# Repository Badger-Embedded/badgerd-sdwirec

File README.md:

# Badgerd SDWireC
[SDWireC](https://badgerd.nl/sdwirec) is a yet another implementation of SDWire of Tizen. In our design we used USB-C interface to interact with the host device or in other words Test Server(TS).

In **sdwirec-hw** folder, you can find the KiCAD project files of SDWireC, hardware design mostly based on Tizen but we changed some of the components since they are out of stock today.

In **sdwirec-sw** folder, you will find the clone of https://git.tizen.org/cgit/tools/testlab/sd-mux which has the software that you need to interact with SDWireC.

## Please follow the instructions in [Quick Start Guide](https://badgerd.nl/sdwirec/#quick-start) to give SDWireC a kickstart!

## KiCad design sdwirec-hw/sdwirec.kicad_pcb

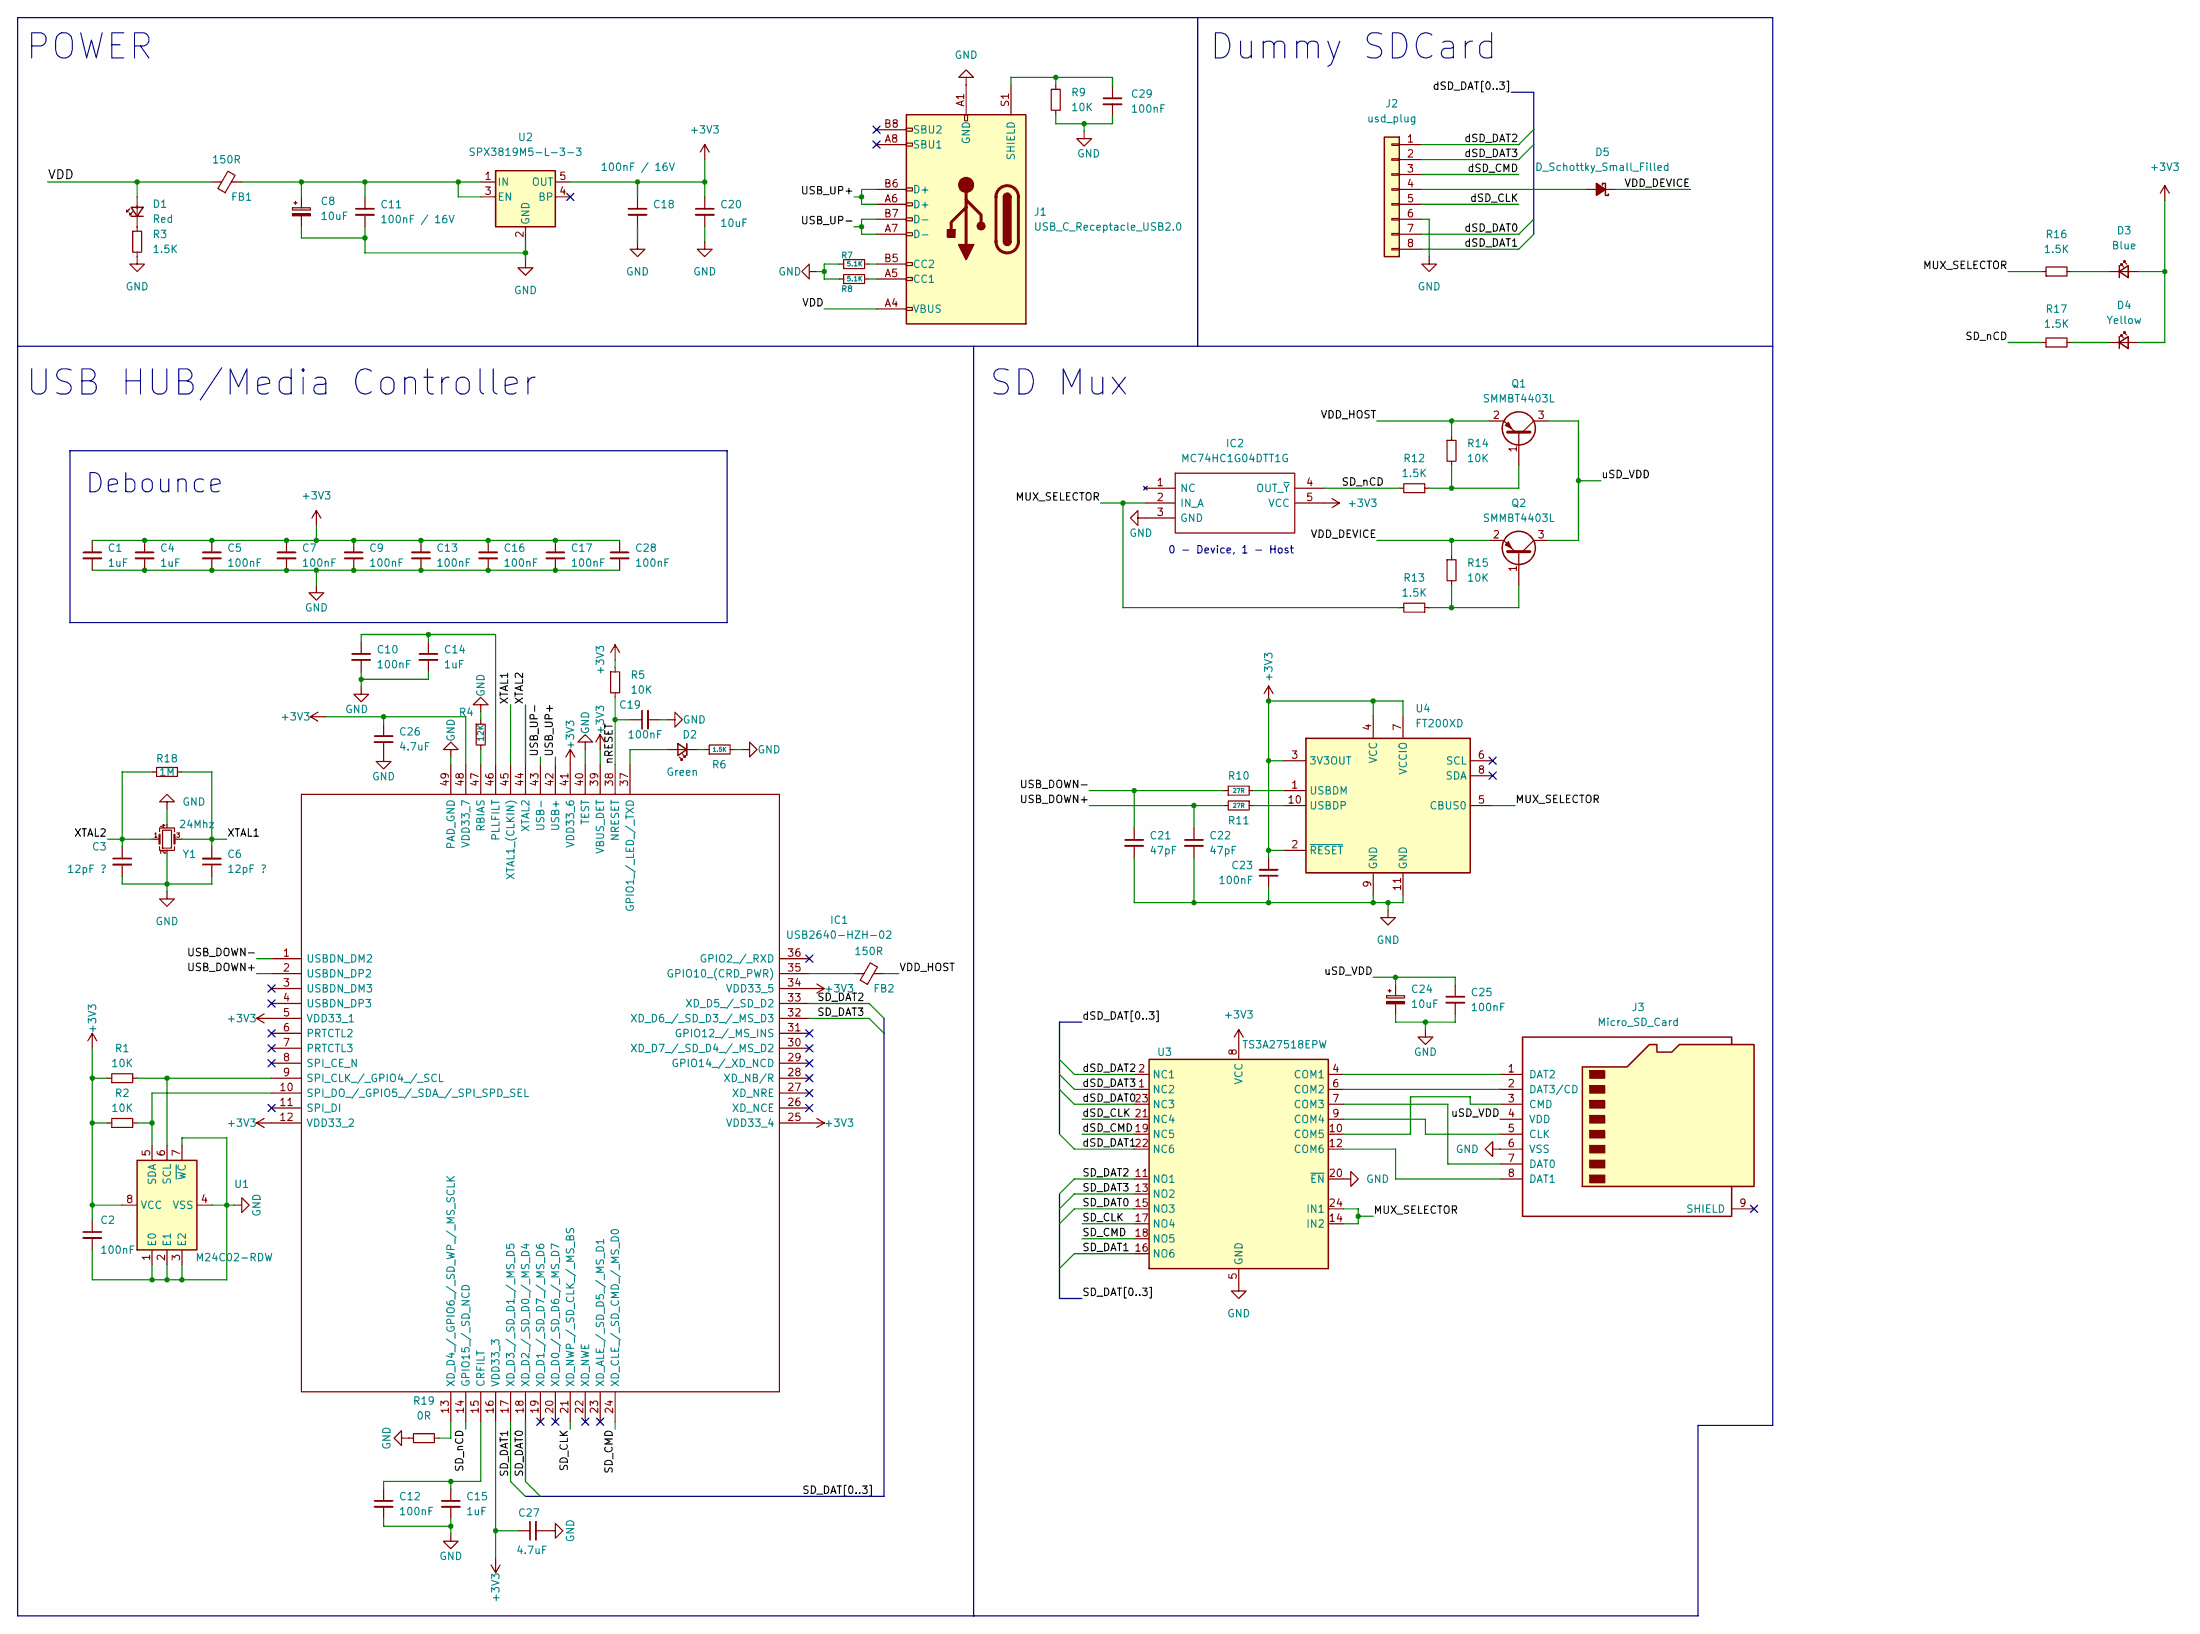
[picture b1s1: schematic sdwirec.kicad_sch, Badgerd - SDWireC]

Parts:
C1, C4, C14, C15: 1uF; C_0603_1608Metric; JLC 0603
C2, C5, C7, C9, C10, C12, C13, C16, C17, C19, C23, C25, C28: 100nF; C_0402_1005Metric; JLC 0402
C3, C6: 12pF ?; C_0402_1005Metric; JLC 0402
C8, C24: 10uF; CP_EIA-3216-18_Kemet-A; JLC CASE-A-3216
C11, C18: 100nF / 16V; C_0402_1005Metric; JLC 0402
C20: 10uF; C_0603_1608Metric; JLC 0603
C21, C22: 47pF; C_0402_1005Metric; JLC 0402
C26, C27: 4.7uF; C_0603_1608Metric; JLC 0603
C29: 100nF; C_0402_1005Metric
D1: Red; LED_0402_1005Metric; JLC 0402
D2: Green; LED_0402_1005Metric; JLC 0402
D3: Blue; LED_0402_1005Metric; JLC 0402
D4: Yellow; LED_0402_1005Metric; JLC 0402
D5: D_Schottky_Small_Filled; D_0402_1005Metric; LCSC Part C2837790
FB1, FB2: 150R; D_0603_1608Metric; JLC 0603
IC1: USB2640-HZH-02; QFN50P700X700X100-49N-D; Mouser Part Number 886-USB2640-HZH-02
IC2: MC74HC1G04DTT1G; SOT95P275X110-5N; Mouser Part Number 863-MC74HC1G04DTT1G
J1: USB_C_Receptacle_USB2.0; USB_C_Receptacle_GCT_USB4105-xx-A_16P_TopMnt_Horizontal; JLC SMD
J2: usd_plug; usd
J3: Micro_SD_Card; 5031821852; LCSC Part C587953
Q1, Q2: SMMBT4403L; SOT-23-3; JLC SOT-23-3
R1, R2, R5, R9, R14, R15: 10K; R_0402_1005Metric; JLC 0402
R3, R6, R12, R13, R16, R17: 1.5K; R_0402_1005Metric; JLC 0402
R4: 12K; R_0402_1005Metric; JLC 0402
R7, R8: 5.1K; R_0402_1005Metric; LCSC Part C25905
R10, R11: 27R; R_0402_1005Metric; JLC 0402
R18: 1M; R_0402_1005Metric
R19: 0R; R_0402_1005Metric; JLC 0402
U1: M24C02-RDW; TSSOP-8_4.4x3mm_P0.65mm; JLC TSSOP-8-3.0mm
U2: SPX3819M5-L-3-3; SOT-23-5; JLC SOT-23-5
U3: TS3A27518EPW; TSSOP-24_4.4x7.8mm_P0.65mm; JLC TSSOP-24
U4: FT200XD; DFN-10-1EP_3x3mm_P0.5mm_EP1.55x2.48mm; JLC DFN-10-EP(3x3)
Y1: 24Mhz; Crystal_SMD_3225-4Pin_3.2x2.5mm; JLC SMD3225-4P

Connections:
+3V3: C1.1, C2.1, C4.1, C5.1, C7.1, C9.1, C13.1, C16.1, C17.1, C18.1, C20.1, C23.2, C26.1, C27.1, C28.1, D3.2 (A), D4.2 (A), IC1.5 (VDD33_1), IC1.12 (VDD33_2), IC1.16 (VDD33_3), IC1.25 (VDD33_4), IC1.34 (VDD33_5), IC1.39 (VBUS_DET), IC1.41 (VDD33_6), IC1.48 (VDD33_7), IC2.5 (VCC), R1.1, R2.1, R5.1, U1.8 (VCC), U2.5 (OUT), U3.8 (VCC), U4.2 (~RESET), U4.3 (3V3OUT), U4.4 (VCC), U4.7 (VCCIO)
/MUX_SELECTOR: IC2.2 (IN_A), R13.2, R16.1, U3.14 (IN2), U3.24 (IN1), U4.5 (CBUS0)
/SD_CLK: IC1.21 (XD_NWP_/_SD_CLK_/_MS_BS), U3.17 (NO4)
/SD_CMD: IC1.24 (XD_CLE_/_SD_CMD_/_MS_D0), U3.18 (NO5)
/SD_DAT0: IC1.18 (XD_D2_/_SD_D0_/_MS_D4), U3.15 (NO3)
/SD_DAT1: IC1.17 (XD_D3_/_SD_D1_/_MS_D5), U3.16 (NO6)
/SD_DAT2: IC1.33 (XD_D5_/_SD_D2), U3.11 (NO1)
/SD_DAT3: IC1.32 (XD_D6_/_SD_D3_/_MS_D3), U3.13 (NO2)
/SD_nCD: IC1.14 (GPIO15_/_SD_NCD), IC2.4 (OUT_~Y), R12.2, R17.1
/USB_DOWN+: C22.1, IC1.2 (USBDN_DP2), R11.2
/USB_DOWN-: C21.1, IC1.1 (USBDN_DM2), R10.1
/USB_UP+: IC1.42 (USB+), J1.A6 (D+), J1.B6 (D+)
/USB_UP-: IC1.43 (USB-), J1.A7 (D-), J1.B7 (D-)
/VDD: D1.2 (A), FB1.1, J1.A4 (VBUS), J1.A9 (VBUS), J1.B4 (VBUS), J1.B9 (VBUS)
/VDD_DEVICE: D5.1 (K), Q2.2 (E), R15.1
/VDD_HOST: FB2.2, Q1.2 (E), R14.1
/XTAL1: C6.2, IC1.45 (XTAL1_(CLKIN)), R18.2, Y1.3
/XTAL2: C3.1, IC1.44 (XTAL2), R18.1, Y1.1
/dSD_CLK: J2.5, U3.21 (NC4)
/dSD_CMD: J2.3, U3.19 (NC5)
/dSD_DAT0: J2.7, U3.23 (NC3)
/dSD_DAT1: J2.8, U3.22 (NC6)
/dSD_DAT2: J2.1, U3.2 (NC1)
/dSD_DAT3: J2.2, U3.1 (NC2)
/nRESET: C19.1, IC1.38 (NRESET), R5.2
/uSD_VDD: C24.1, C25.1, J3.4 (VDD), Q1.3 (C), Q2.3 (C)
GND: C1.2, C2.2, C3.2, C4.2, C5.2, C6.1, C7.2, C8.2, C9.2, C10.2, C11.2, C12.2, C13.2, C14.2, C15.2, C16.2, C17.2, C18.2, C19.2, C20.2, C21.2, C22.2, C23.1, C24.2, C25.2, C26.2, C27.2, C28.2, C29.2, IC1.40 (TEST), IC1.49 (PAD_GND), IC2.3 (GND), J1.A1 (GND), J1.A12 (GND), J1.B1 (GND), J1.B12 (GND), J2.6, J3.6 (VSS), R3.2, R4.1, R6.2, R7.1, R8.1, R9.2, R19.1, U1.1 (E0), U1.2 (E1), U1.3 (E2), U1.4 (VSS), U1.7 (~WC), U2.2 (GND), U3.5 (GND), U3.20 (~EN), U4.9 (GND), U4.11 (GND), Y1.2, Y1.4
unnamed: C10.1, C14.1, IC1.46 (PLLFILT)
unnamed: C8.1, C11.1, FB1.2, U2.1 (IN), U2.3 (EN)
unnamed: C12.1, C15.1, IC1.15 (CRFILT)
unnamed: C29.1, J1.S1 (SHIELD), R9.1
unnamed: D1.1 (K), R3.1
unnamed: D2.1 (K), R6.1
unnamed: D2.2 (A), IC1.37 (GPIO1_/_LED_/_TXD)
unnamed: D3.1 (K), R16.2
unnamed: D4.1 (K), R17.2
unnamed: FB2.1, IC1.35 (GPIO10_(CRD_PWR))
unnamed: IC1.9 (SPI_CLK_/_GPIO4_/_SCL), R1.2, U1.6 (SCL)
unnamed: IC1.10 (SPI_DO_/_GPIO5_/_SDA_/_SPI_SPD_SEL), R2.2, U1.5 (SDA)
unnamed: IC1.13 (XD_D4_/_GPIO6_/_SD_WP_/_MS_SCLK), R19.2
unnamed: IC1.47 (RBIAS), R4.2
unnamed: J1.A5 (CC1), R8.2
unnamed: J1.B5 (CC2), R7.2
unnamed: D5.2 (A), J2.4
unnamed: J3.1 (DAT2), U3.4 (COM1)
unnamed: J3.2 (DAT3/CD), U3.6 (COM2)
unnamed: J3.3 (CMD), U3.10 (COM5)
unnamed: J3.5 (CLK), U3.9 (COM4)
unnamed: J3.7 (DAT0), U3.7 (COM3)
unnamed: J3.8 (DAT1), U3.12 (COM6)
unnamed: Q1.1 (B), R12.1, R14.2
unnamed: Q2.1 (B), R13.1, R15.2
unnamed: R10.2, U4.1 (USBDM)
unnamed: R11.1, U4.10 (USBDP)

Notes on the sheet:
0 - Device, 1 - Host
POWER
SD Mux
USB HUB/Media Controller
Dummy SDCard
Debounce

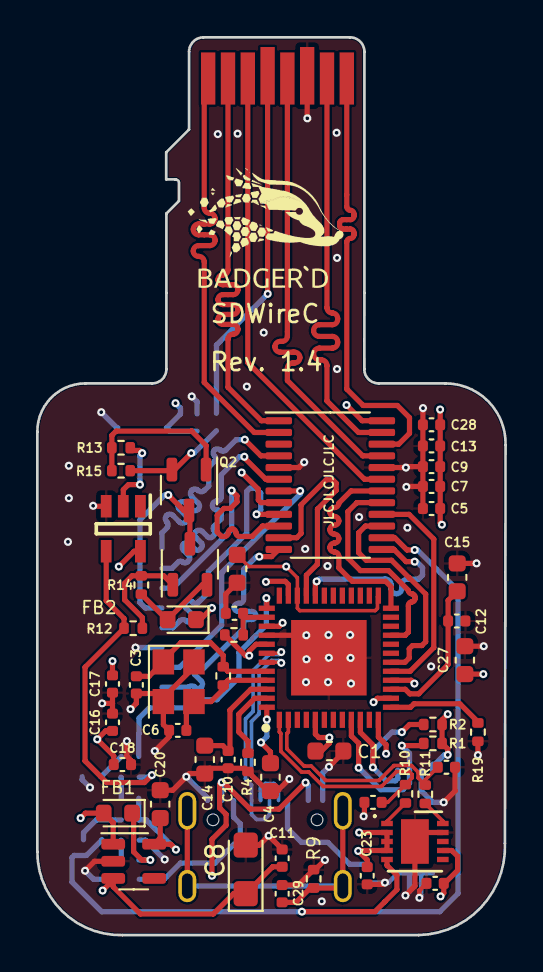
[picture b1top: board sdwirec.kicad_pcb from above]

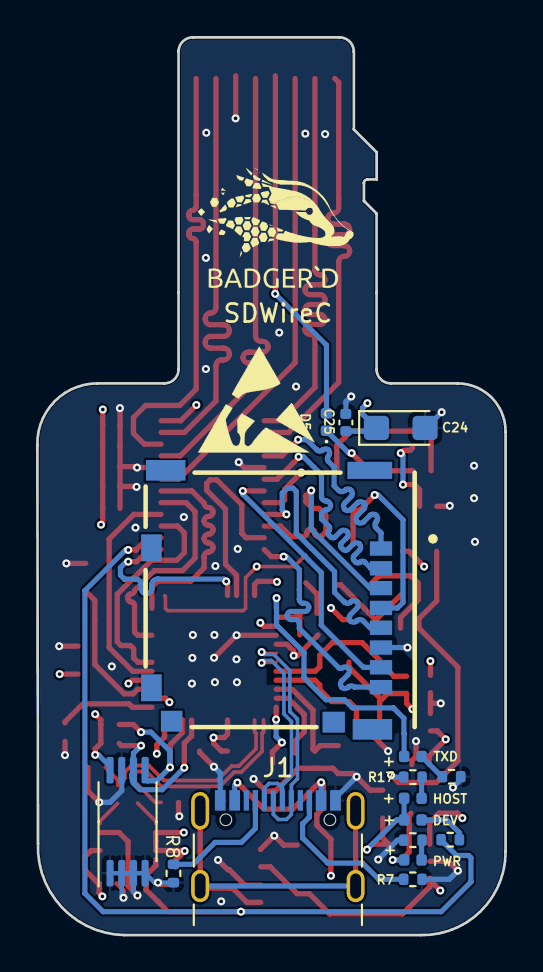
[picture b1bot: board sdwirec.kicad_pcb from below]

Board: 4 copper layers, 26.0 x 49.9 mm, 67 parts (16 on the bottom side), 54 nets.

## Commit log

2023-01-17 Add SDWire software into repo
2023-01-17 Add readme file
2023-03-26 Rev 1.2
2023-05-22 Add snapcraft packaging script
2023-07-17 Rev 1.3
2023-07-17 squash! Rev 1.3
2024-09-06 add schottky diode to vdd_device line
2024-09-06 add schottky diode on vdd_device line
2024-09-06 squash! add schottky diode on vdd_device line
2024-10-14 sdwire-cli: add cross platform alternative #3
2024-10-14 sdwire-cli: fix usbbus detection #3
2024-10-14 sdwire-cli: initialize poetry project for crossplatform cli #3
2024-10-14 actions: add github actions to build python package
2024-10-14 actions: add publish to pypi jobs
2024-10-14 actions: add release.yml
2024-10-14 actions: use sigstore version 3
2024-10-14 fixup! actions: use sigstore version 3
